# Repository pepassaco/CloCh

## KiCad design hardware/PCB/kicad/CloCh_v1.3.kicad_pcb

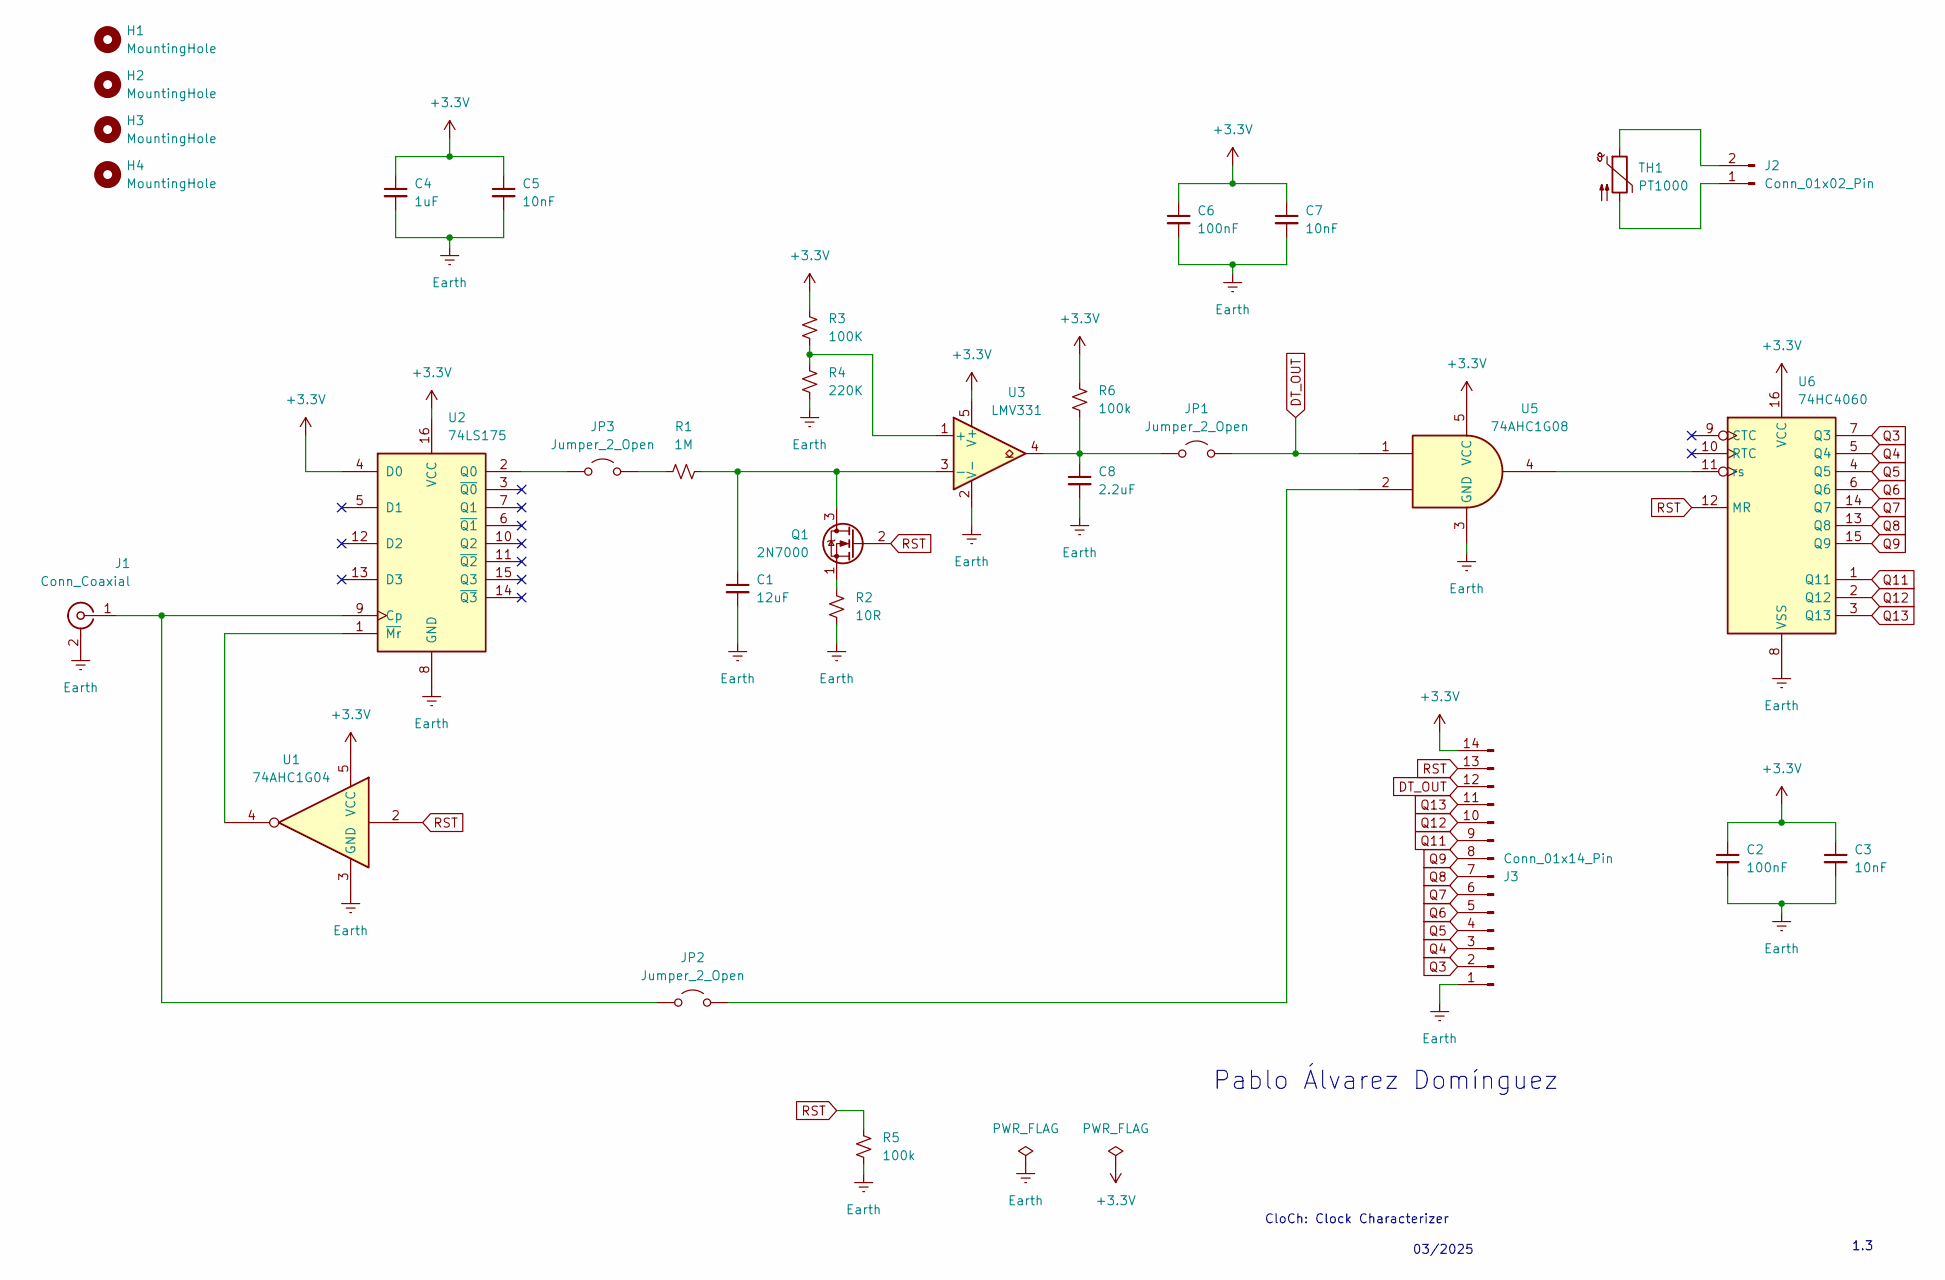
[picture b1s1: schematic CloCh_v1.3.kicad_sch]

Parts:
C1: 12uF; C_Rect_L28.0mm_W8.0mm_P22.50mm_MKS4
C2, C6: 100nF; C_0805_2012Metric
C3, C5, C7: 10nF; C_0805_2012Metric
C4: 1uF; C_0805_2012Metric
C8: 2.2uF; C_0805_2012Metric
H1, H2, H3, H4: MountingHole; MountingHole_4.3mm_M4_ISO7380
J1: Conn_Coaxial; SMA_Amphenol_132289_EdgeMount
J2: Conn_01x02_Pin; PinHeader_1x02_P2.54mm_Vertical
J3: Conn_01x14_Pin; PinHeader_1x14_P2.54mm_Vertical
JP1, JP2, JP3: Jumper_2_Open; SolderJumper-2_P1.3mm_Open_RoundedPad1.0x1.5mm
Q1: 2N7000; TO-92_Inline
R1: 1M; R_Axial_DIN0411_L9.9mm_D3.6mm_P12.70mm_Horizontal
R2: 10R; R_0805_2012Metric
R3: 100K; R_0805_2012Metric
R4: 220K; R_0805_2012Metric
R5, R6: 100k; R_0805_2012Metric
TH1: PT1000; R_Axial_DIN0204_L3.6mm_D1.6mm_P1.90mm_Vertical
U1: 74AHC1G04; SOT-353_SC-70-5
U2: 74LS175; SOIC127P600X175-16N
U3: LMV331; SOT-353_SC-70-5
U5: 74AHC1G08; SC-74A-5_1.55x2.9mm_P0.95mm
U6: 74HC4060; SO-16_3.9x9.9mm_P1.27mm

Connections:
+3.3V: C2.1, C3.1, C4.1, C5.1, C6.1, C7.1, J3.14, R3.2, R6.1, U1.5 (VCC), U2.4 (D0), U2.16 (VCC), U3.5 (V+), U5.5 (VCC), U6.16 (VCC)
DT_OUT: J3.12, JP1.2 (B), U5.1
Earth: C1.2, C2.2, C3.2, C4.2, C5.2, C6.2, C7.2, C8.2, J1.2 (Ext), J3.1, R2.1, R4.1, R5.2, U1.3 (GND), U2.8 (GND), U3.2 (V-), U5.3 (GND), U6.8 (VSS)
unnamed: J1.1 (In), JP2.1 (A), U2.9 (Cp)
unnamed: J2.1, TH1.2
unnamed: J2.2, TH1.1
unnamed: C8.1, JP1.1 (A), R6.2, U3.4
unnamed: JP2.2 (B), U5.2
unnamed: JP3.1 (A), U2.2 (Q0)
unnamed: JP3.2 (B), R1.1
unnamed: C1.1, Q1.3 (D), R1.2, U3.3 (-)
unnamed: Q1.1 (S), R2.2
unnamed: U1.4, U2.1 (~Mr)
unnamed: R3.1, R4.2, U3.1 (+)
unnamed: U5.4, U6.11 (rs)
Q3: J3.2, U6.7 (Q3)
Q4: J3.3, U6.5 (Q4)
Q5: J3.4, U6.4 (Q5)
Q6: J3.5, U6.6 (Q6)
Q7: J3.6, U6.14 (Q7)
Q8: J3.7, U6.13 (Q8)
Q9: J3.8, U6.15 (Q9)
Q11: J3.9, U6.1 (Q11)
Q12: J3.10, U6.2 (Q12)
Q13: J3.11, U6.3 (Q13)
RST: J3.13, Q1.2 (G), R5.1, U1.2, U6.12 (MR)

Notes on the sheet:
03/2025
CloCh: Clock Characterizer
1.3
Pablo Álvarez Domínguez

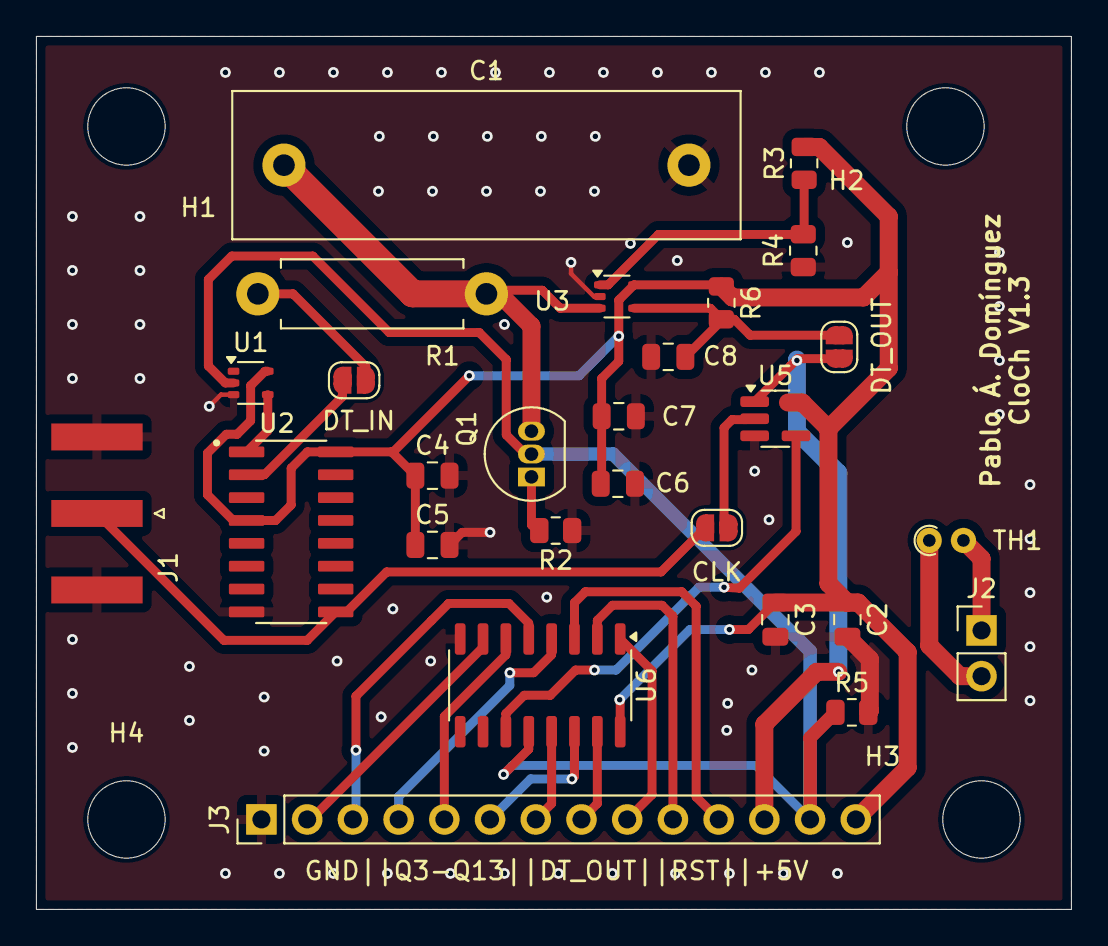
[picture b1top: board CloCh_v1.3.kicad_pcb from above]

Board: 2 copper layers, 57.5 x 48.5 mm, 31 parts (0 on the bottom side), 26 nets.

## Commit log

2025-10-24 Initial commit with firmware and data
2025-10-24 Added PCB documentation
2025-10-25 New plotter, adapted experiment for longer runs
2025-10-28 Modified temperature correction
2025-10-31 Added plotter for the paper and changed temperature correction
2025-11-06 Improved plots
